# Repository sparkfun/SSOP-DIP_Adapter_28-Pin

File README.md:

SSOP DIP Adapter 28-Pin
=======================
[
*SparkFun SSOP to DIP Adapter 28-Pin(BOB-00500)*](https://www.sparkfun.com/products/500)

This breakout board breaks out the SSOP devices with any pin count up to 28 pins to a standard 0.1" spacing. 
Repository Contents
-------------------
* **/Hardware** - All Eagle design files (.brd, .sch)

License Information
-------------------
The hardware is released under [Creative Commons ShareAlike 4.0 International](https://creativecommons.org/licenses/by-sa/4.0/).
The code is beerware; if you see me (or any other SparkFun employee) at the local, and you've found our code helpful, please buy us a round!

Distributed as-is; no warranty is given.

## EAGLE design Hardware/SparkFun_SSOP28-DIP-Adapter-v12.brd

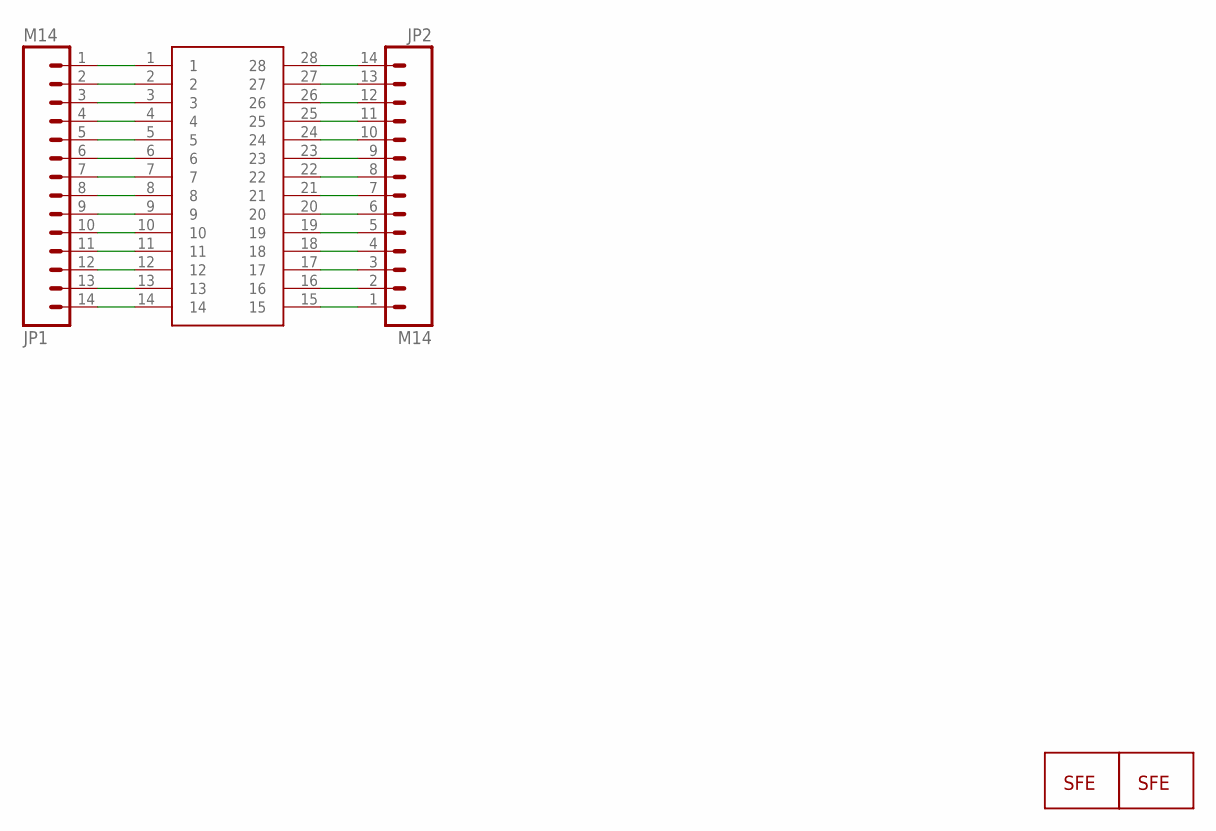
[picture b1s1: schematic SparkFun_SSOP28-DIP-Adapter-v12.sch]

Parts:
JP1, JP2: M14; 1X14
U$1: LOGO-SFESK; SFE-LOGO-FLAME
U$2: SSOP28; SSOP28DB
U$5: LOGO-SFENEW; SFE-NEW-WEBLOGO

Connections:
unnamed: JP2.1, U$2.15
unnamed: JP2.2, U$2.16
unnamed: JP2.3, U$2.17
unnamed: JP2.4, U$2.18
unnamed: JP2.5, U$2.19
unnamed: JP2.6, U$2.20
unnamed: JP2.7, U$2.21
unnamed: JP2.8, U$2.22
unnamed: JP2.9, U$2.23
unnamed: JP2.10, U$2.24
unnamed: JP2.11, U$2.25
unnamed: JP2.12, U$2.26
unnamed: JP2.13, U$2.27
unnamed: JP2.14, U$2.28
unnamed: JP1.1, U$2.1
unnamed: JP1.2, U$2.2
unnamed: JP1.3, U$2.3
unnamed: JP1.4, U$2.4
unnamed: JP1.5, U$2.5
unnamed: JP1.6, U$2.6
unnamed: JP1.7, U$2.7
unnamed: JP1.8, U$2.8
unnamed: JP1.9, U$2.9
unnamed: JP1.10, U$2.10
unnamed: JP1.11, U$2.11
unnamed: JP1.12, U$2.12
unnamed: JP1.13, U$2.13
unnamed: JP1.14, U$2.14

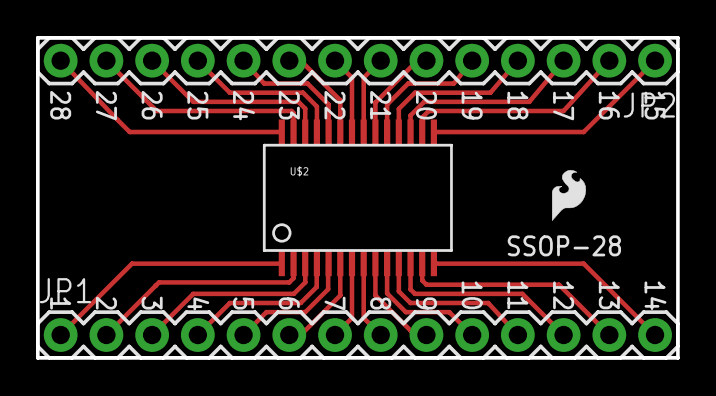
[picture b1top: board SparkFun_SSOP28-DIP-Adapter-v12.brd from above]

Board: 2 copper layers, 35.6 x 17.8 mm, 5 parts (1 on the bottom side), 28 nets.

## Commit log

2015-01-06 Initial hardware commit
